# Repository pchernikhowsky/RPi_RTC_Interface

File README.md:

# Raspberry Pi RTC / Interface Board

## Description

A Raspberry Pi HAT-style interface board that includes:
* [DS3231](https://www.analog.com/en/products/ds3231.html) highly accurate real-time clock (RTC) with replaceable battery backup
* [DS18B20](https://www.analog.com/en/products/ds18b20.html) precision temperature sensor
* 3-pin header terminal for access to the Pi serial console (`/dev/ttyS0` a.k.a. `/dev/serial0`) connection
* Screw terminals for connecting [I2C](https://en.wikipedia.org/wiki/I%C2%B2C) devices (such as displays, sensors, D/A and A/D converters, etc.)
* Screw terminals for connecting [1-Wire](https://en.wikipedia.org/wiki/1-Wire) devices (such as additional DS18B20 sensors and other 1-Wire compatible devices)

## Hardware
### Electrical Interfaces

> [!CAUTION]
> **The Raspberry Pi uses non-5V tolerant 3.3V GPIO**. This includes the `SDA`, `SCL`, and `DQ` signals and the `RXD` and `TXD` serial port pins. Connecting any of these signals to higher voltages may damage your Raspberry Pi.

Two sets of screw terminals are provided:
1. A four-terminal I2C connector with 3.3V power, `SDA`, `SCL`, and ground.
2. A three-terminal 1-Wire connector with 3.3V power, `DQ`, and ground.

Pull-ups for each of the `SDA`, `SCL` and `DQ` signals are provided. An LED indicates that 3.3V power is present at the terminals. 

> [!NOTE]
> As per the spec for the [onboard 5V to 3.3V LDO](https://www.diodes.com/assets/Datasheets/AP7361EA.pdf), the I2C and 1-Wire interfaces are able to supply up to 1 amp of power to connected devices. If the 3.3V power output from the I2C or 1-Wire interfaces is overloaded or shorted to ground (i.e., current draw exceeds 1.5 amps), the LDO regulator will automatically shutdown and the 3.3V power LED will extinguish. Removing the overload/short will automatically restore the 3.3V power supply.

A 3-pin 0.1 in. spacing header connector provides access to the `/dev/ttyS0` serial device signals `RXD`, `TXD` and ground. These are 3.3V logic signals and require external level shifters for compatibility with [RS-232 signal](https://en.wikipedia.org/wiki/RS-232) voltage levels. Many 3.3V to USB interface cables are available for purchase from Amazon, eBay, etc.

> [!NOTE]
> * `RXD` refers to serial data received by (input to) the Pi.
> * `TXD` refers to serial data sent from (output from) the Pi.

### Hardware Construction and Setup

The PCB is designed to mount on any Raspberry Pi Model A+/B+ or later (i.e., any Pi with the 40 pin expansion connecter). While the PCB conforms to the Pi HAT [physical specification](https://github.com/raspberrypi/hats/blob/master/hat-board-mechanical.pdf) there is no EEPROM for full autoconfiguration. As such, this project does not claim 100% compatibility with the Pi HAT specification. 

The schematic and PCB layout were designed using [KiCad 8.0](https://www.kicad.org/). A full hardware design including [schematic](schematic.pdf) and [PCB layout](RPi_RTC_Interface_model.jpg) in KiCad format are provided. If you prefer, the [gerber files](RPi_RTC_interface_gerbers.zip) can be directly uploaded to most PCB manufacturer sites (avoiding the need to install KiCad).

A Microsoft Excel [bill of materials](RPi_RTC_interface_BOM.xlsx) is also included.

> [!TIP]
> I prefer to order my PCBs from [JLCPCB](https://jlcpcb.com/) and components from [DigiKey](https://digikey.com). The total parts cost (excluding the PCB and CR2032 coin cell) is approximately $24 USD (as of September 2024).

Following are unpopulated and populated photos of the front and rear of the PCB.

## Updating the Raspberry Pi OS to support the peripherals

1. [Configure the kernel and install the necessary RTC packages.](https://pimylifeup.com/raspberry-pi-rtc/)
2. [Enable the 1-Wire interface.](https://www.circuitbasics.com/raspberry-pi-ds18b20-temperature-sensor-tutorial/)
 
## Version history

* 1.0
    * Initial Release

## License

This project is licensed under the GPL-3.0 License. See the [LICENSE](LICENSE) file for details.

## Acknowledgments

PCB dimensions and layout courtesy:
* [RPi_Hat_Template](https://github.com/devbisme/RPi_Hat_Template)

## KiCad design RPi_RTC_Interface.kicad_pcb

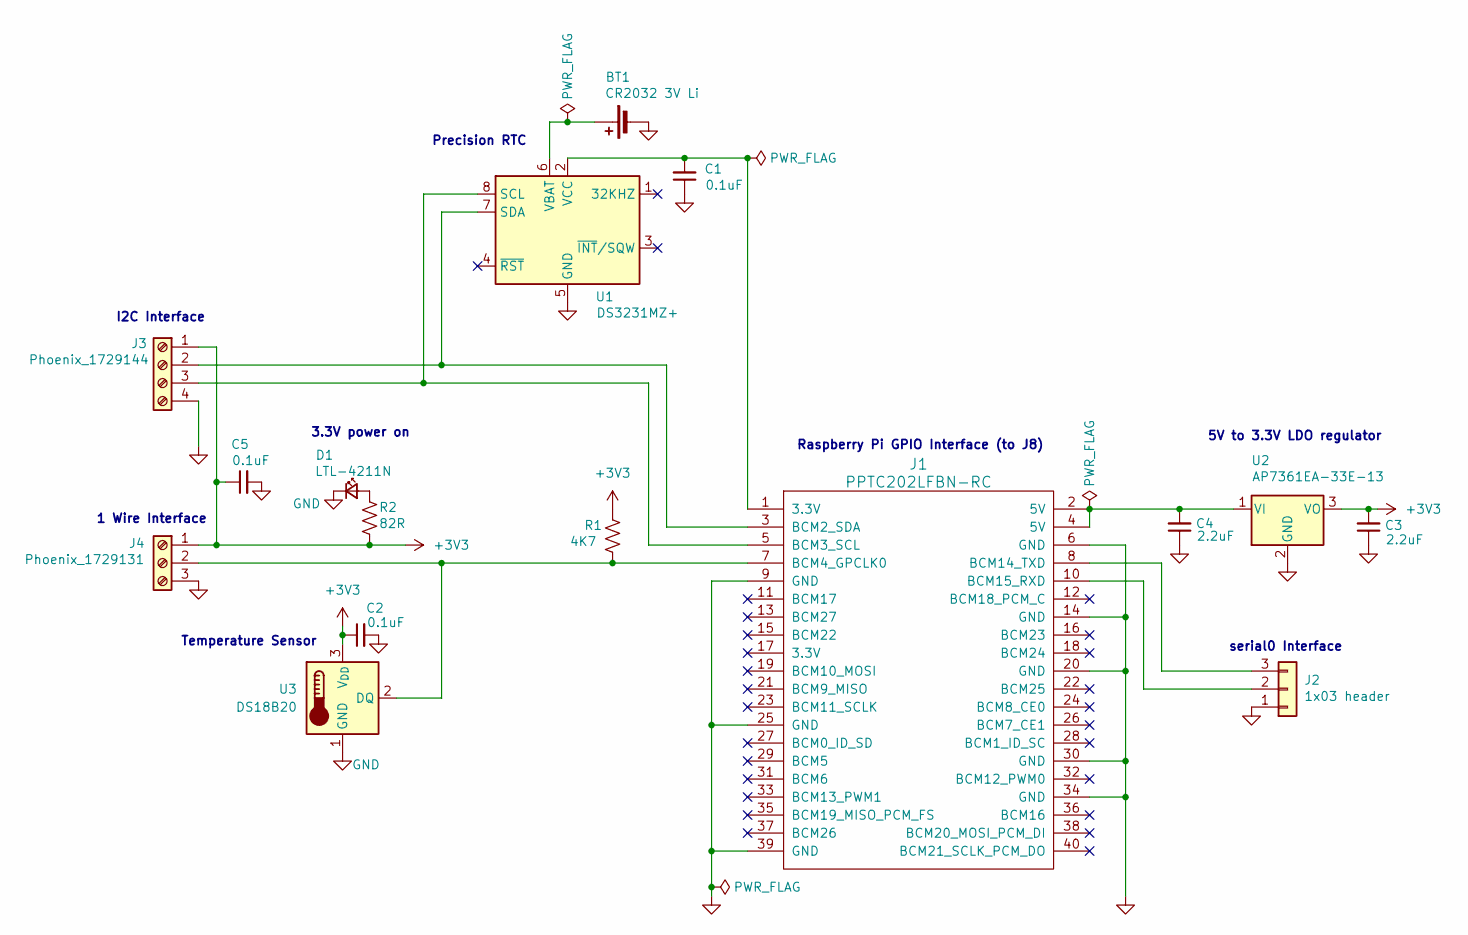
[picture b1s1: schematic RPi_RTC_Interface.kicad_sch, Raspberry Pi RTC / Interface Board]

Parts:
BT1: CR2032 3V Li; BatteryHolder_Keystone_103_1x20mm
C1, C2, C5: 0.1uF; C_Disc_D3.0mm_W1.6mm_P2.50mm
C3, C4: 2.2uF; CAPRB250W50L400T250H550
D1: LTL-4211N; LED_D3.0mm
J1: PPTC202LFBN-RC; RPI_PinSocket_2x20
J2: 1x03 header; PinHeader_1x03_P2.54mm_Vertical
J3: Phoenix_1729144; TerminalBlock_Phoenix_MKDS-1,5-4-5.08_1x04_P5.08mm_Horizont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
J4: Phoenix_1729131; TerminalBlock_Phoenix_MKDS-1,5-3-5.08_1x03_P5.08mm_Horizont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
R1: 4K7; R_Axial_DIN0207_L6.3mm_D2.5mm_P10.16mm_Horizontal
R2: 82R; R_Axial_DIN0207_L6.3mm_D2.5mm_P10.16mm_Horizontal
U1: DS3231MZ+; SOIC-8_3.9x4.9mm_P1.27mm
U2: AP7361EA-33E-13; SOT-223-3_TabPin2
U3: DS18B20; TO-92_Inline

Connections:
+3V3: C2.1, C3.2, C5.1, J3.1, J4.1, R1.1, R2.2, U2.3 (VO), U3.3 (V_{DD})
GND: BT1.2 (-), C1.1, C2.2, C3.1, C4.1, C5.2, D1.1 (K), J1.6 (GND), J1.9 (GND), J1.14 (GND), J1.20 (GND), J1.25 (GND), J1.30 (GND), J1.34 (GND), J1.39 (GND), J2.1, J3.4, J4.3, U1.5 (GND), U2.2 (GND), U3.1 (GND)
unnamed: BT1.1 (+), U1.6 (VBAT)
unnamed: D1.2 (A), R2.1
unnamed: J1.3 (BCM2_SDA), J3.2, U1.7 (SDA)
unnamed: J1.5 (BCM3_SCL), J3.3, U1.8 (SCL)
unnamed: J1.7 (BCM4_GPCLK0), J4.2, R1.2, U3.2 (DQ)
unnamed: J1.8 (BCM14_TXD), J2.3
unnamed: J1.10 (BCM15_RXD), J2.2
unnamed: C1.2, J1.1 (3.3V), U1.2 (VCC)
unnamed: C4.2, J1.2 (5V), J1.4 (5V), U2.1 (VI)

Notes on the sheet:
1 Wire Interface
I2C Interface
3.3V power on
5V to 3.3V LDO regulator
Precision RTC
serial0 Interface
Raspberry Pi GPIO Interface (to J8)
Temperature Sensor

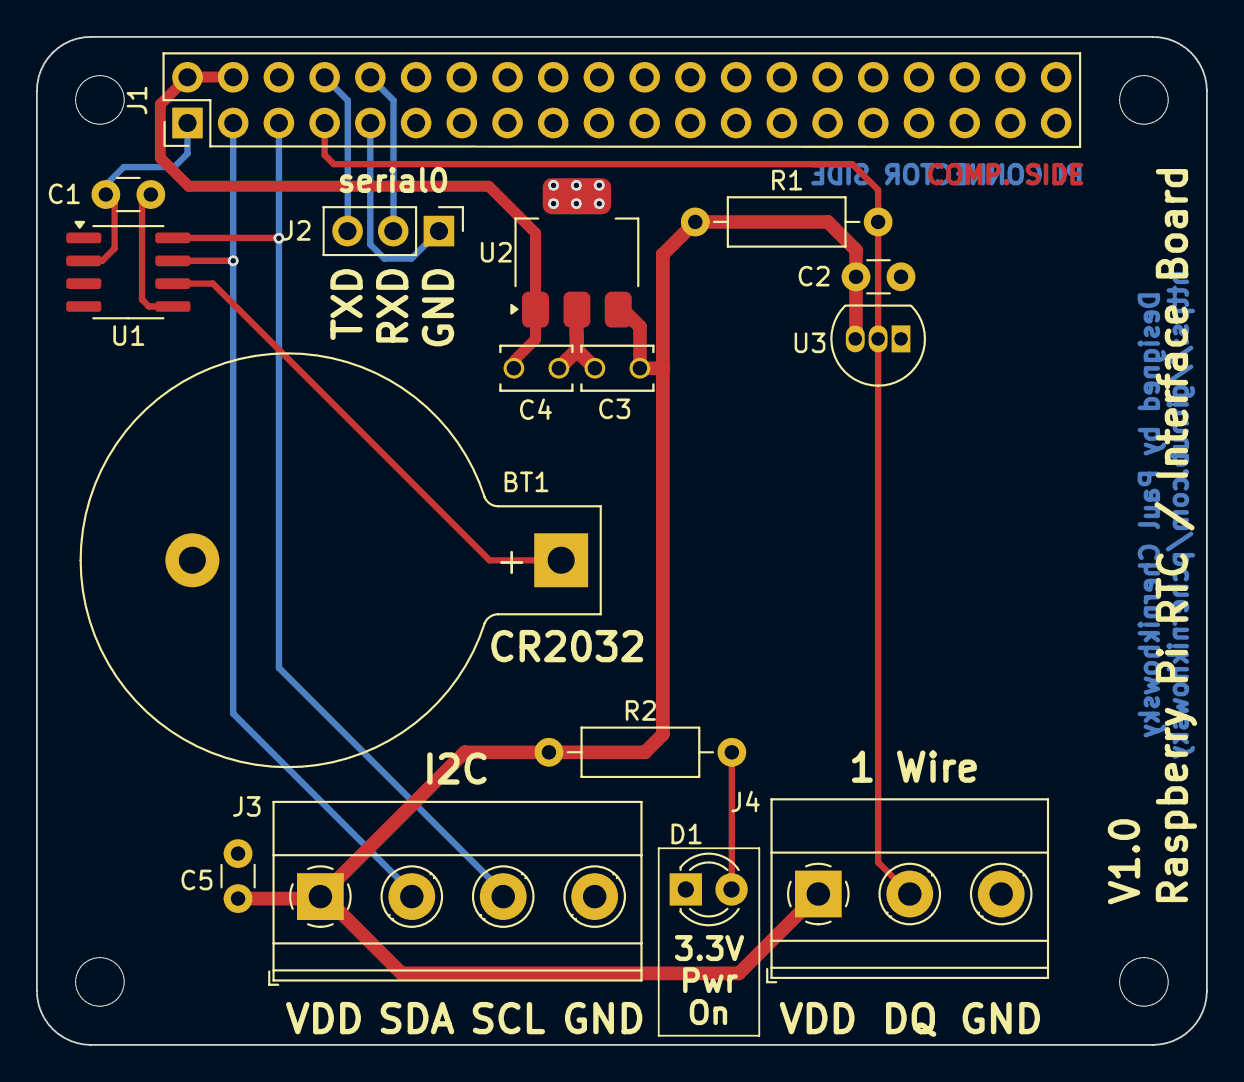
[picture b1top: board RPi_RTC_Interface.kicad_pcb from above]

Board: 2 copper layers, 65.0 x 56.0 mm, 20 parts (0 on the bottom side), 11 nets.

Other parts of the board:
REF1, REF2, REF3, REF4: MountingHole_2.7mm

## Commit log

2024-09-02 remove gerbers/*
2024-09-02 remove .gitattributes
2024-09-02 remove
2024-09-02 Added schematic PDF
2024-09-02 Added PCB photos
2024-09-02 Added KiCad 3D model image
2024-09-02 Remove old BOM
2024-09-02 Updated gerbers

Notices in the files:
RPi_RTC_Interface.kicad_sch:
(c) 2024 Paul Chernikhowsky
